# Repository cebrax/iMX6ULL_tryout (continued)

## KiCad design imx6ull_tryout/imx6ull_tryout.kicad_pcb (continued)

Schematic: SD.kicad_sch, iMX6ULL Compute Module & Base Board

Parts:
C12, C23, C53, C54, C56, C57, C58: 1uF; IPC-SMD-C-0402; Voltage 10V
C51, C52, C55: 22uF; IPC-SMD-C-0603; Voltage 6.3V
P1: 47352-1001; Connector-uSD-Molex-47352-1001
R14, R15: 10k; IPC-SMD-R-0402
U1: iMX6ULL; BGA289C80P17X17_1400X1400X132N
U3: FEMDRM008G-58A39; 153-VFBGA

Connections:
+3V3: C12.1, C23.1, C51.1, C52.1, C53.1, C54.1, P1.4 (Vdd), R14.1, R15.1, U1.C4 (NVCC_SD1), U3.E6 (VCC), U3.F5 (VCC), U3.J10 (VCC), U3.K9 (VCC); also elsewhere on the board
/SD/eMMC/SD1_CLK: P1.5 (CLK), U1.C1 (SD1_CLK), U3.M6 (CLK)
/SD/eMMC/SD1_CMD: P1.3 (CMD), R15.2, U1.C2 (SD1_CMD), U3.M5 (CMD)
/SD/eMMC/SD1_DATA0: P1.7 (DAT0), R14.2, U1.B3 (SD1_DATA0), U3.A3 (DAT0)
/SD/eMMC/SD1_DATA1: P1.8 (DAT1), U1.B2 (SD1_DATA1), U3.A4 (DAT1)
/SD/eMMC/SD1_DATA2: P1.1 (DAT2), U1.B1 (SD1_DATA2), U3.A5 (DAT2)
/SD/eMMC/SD1_DATA3: P1.2 (DAT3/CD), U1.A2 (SD1_DATA3), U3.B2 (DAT3)
GND: C12.2, C23.2, C51.2, C52.2, C53.2, C54.2, C55.2, C56.2, C57.2, C58.2, P1.6 (Vss), P1.10 (Shield), U3.A6 (VSS), U3.C4 (VSSQ), U3.E7 (VSS), U3.G5 (VSS), U3.H10 (VSS), U3.J5 (VSS), U3.K8 (VSS), U3.N2 (VSSQ), U3.N5 (VSSQ), U3.P4 (VSSQ), U3.P6 (VSSQ); also elsewhere on the board
unnamed: C55.1, C56.1, C57.1, U3.C6 (VCCQ), U3.M4 (VCCQ), U3.N4 (VCCQ), U3.P3 (VCCQ), U3.P5 (VCCQ)
unnamed: C58.1, U3.C2 (VDDI)

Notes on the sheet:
DAT0 and CMD are open drain at the time of initialization
eMMC Option
DNP, No Footprints For future reference only
uSD Option

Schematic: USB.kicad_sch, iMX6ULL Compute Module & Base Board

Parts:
C28, C68: 1uF; IPC-SMD-C-0402; Voltage 10V
C69: 22uF; IPC-SMD-C-0603; Voltage 6.3V
P4, P5: DS1095-WNR0; Connector-USB-A-Female-DS1095-WNR0
U1: iMX6ULL; BGA289C80P17X17_1400X1400X132N

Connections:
+5V: C28.1, P4.1, P5.1, U1.T12 (USB_OTG1_VBUS), U1.U12 (USB_OTG2_VBUS); also elsewhere on the board
/USB/USB1_D_N: P4.2, U1.T15 (USB_OTG1_DN)
/USB/USB1_D_P: P4.3, U1.U15 (USB_OTG1_DP)
/USB/USB2_D_N: P5.2, U1.T13 (USB_OTG2_DN)
/USB/USB2_D_P: P5.3, U1.U13 (USB_OTG2_DP)
GND: C28.2, C68.2, C69.2, P4.5, P5.5; also elsewhere on the board
unnamed: C68.1, C69.1, U1.R12 (VDD_USB_CAP)

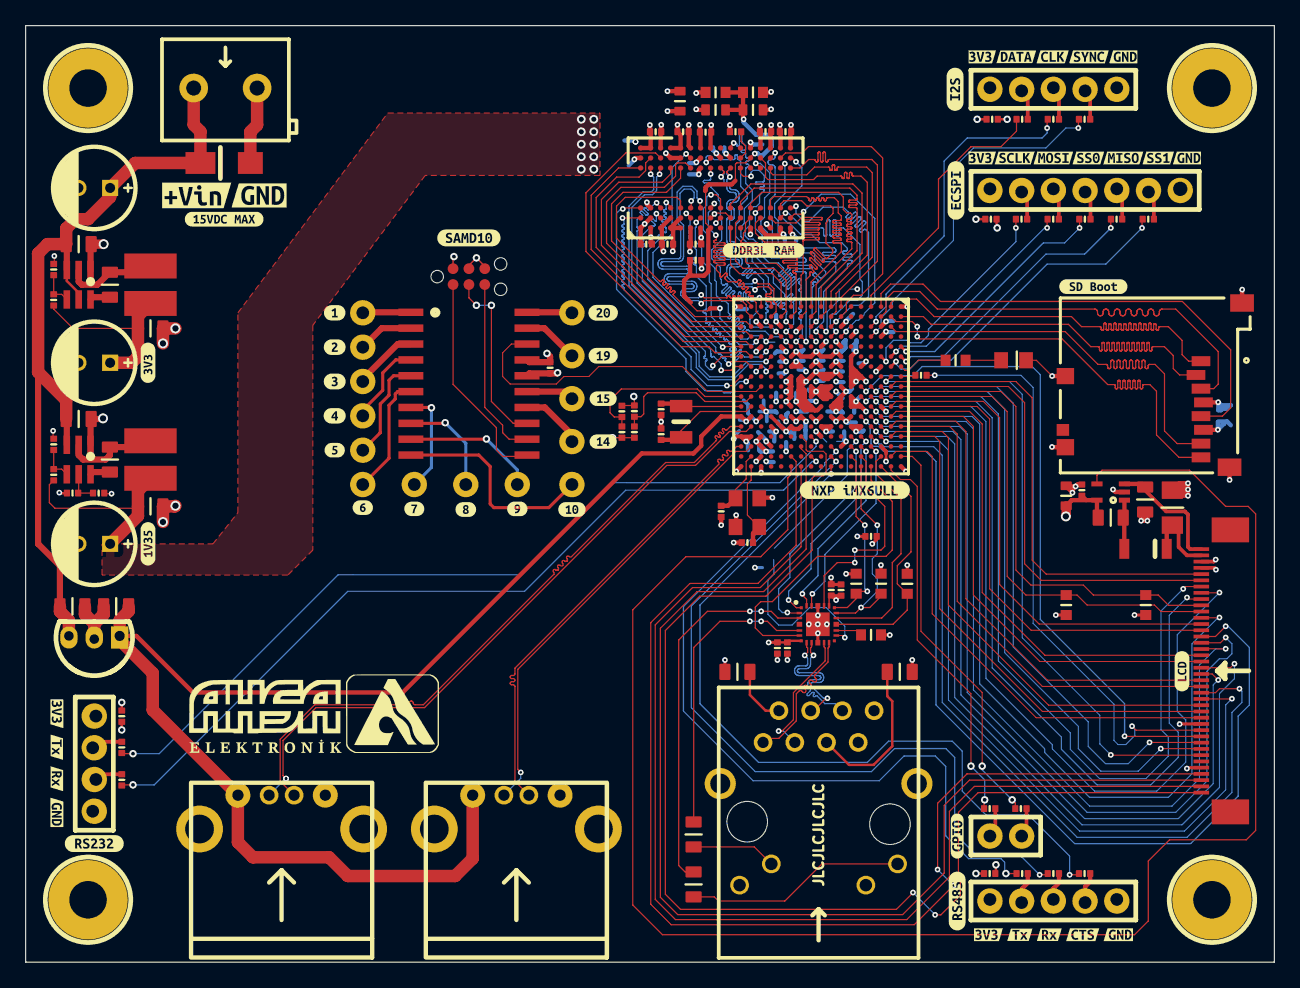
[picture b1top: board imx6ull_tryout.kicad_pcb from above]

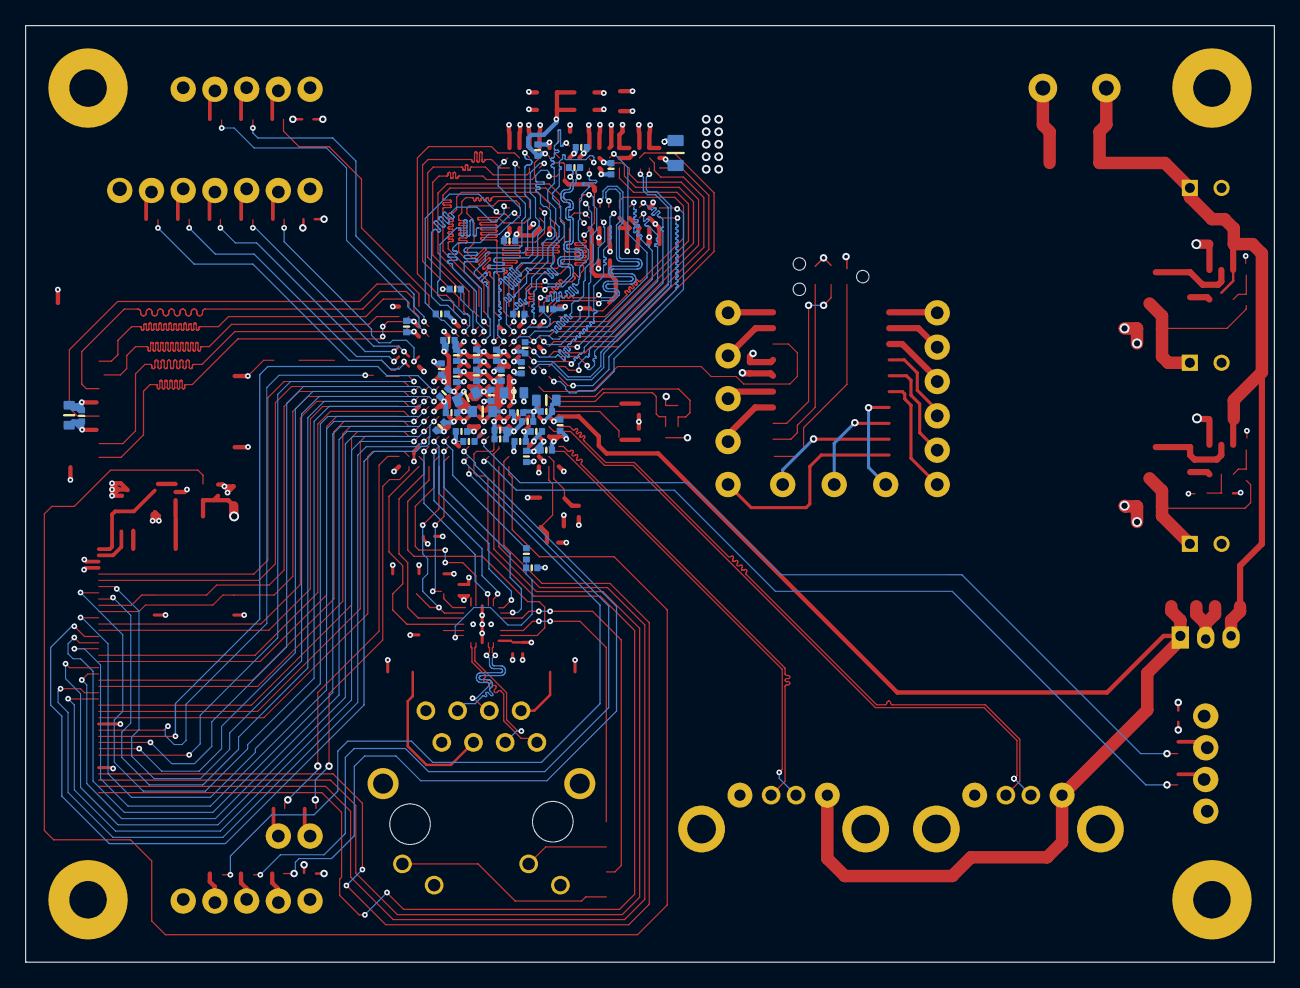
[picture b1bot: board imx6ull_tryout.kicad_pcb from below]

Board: 4 copper layers, 100.0 x 75.0 mm, 222 parts (45 on the bottom side), 199 nets.

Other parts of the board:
C60#2: 1uF; IPC-SMD-C-0402
svg2mod, svg2mod#2, svg2mod#3, svg2mod#4, svg2mod#5, svg2mod#6, svg2mod#7, svg2mod#8, svg2mod#9, svg2mod#10, svg2mod#11, svg2mod#12, svg2mod#13, svg2mod#14, svg2mod#15, svg2mod#16, svg2mod#17, svg2mod#18, svg2mod#19, svg2mod#20, svg2mod#21, svg2mod#22, svg2mod#23, svg2mod#24, svg2mod#25, svg2mod#26, svg2mod#27, svg2mod#28, svg2mod#29, svg2mod#30, svg2mod#31, svg2mod#32, svg2mod#33, svg2mod#34, svg2mod#35, svg2mod#36, svg2mod#37, svg2mod#38, svg2mod#39, svg2mod#40, svg2mod#41, svg2mod#42, svg2mod#43, svg2mod#44, svg2mod#45, svg2mod#46, svg2mod#47, svg2mod#48, svg2mod#49, svg2mod#50: G***; svg2mod

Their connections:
+3V3: C60#2.1; also elsewhere on the board
GND: C60#2.2; also elsewhere on the board
